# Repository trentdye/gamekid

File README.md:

# gamekid
Source files for my portable gaming device.

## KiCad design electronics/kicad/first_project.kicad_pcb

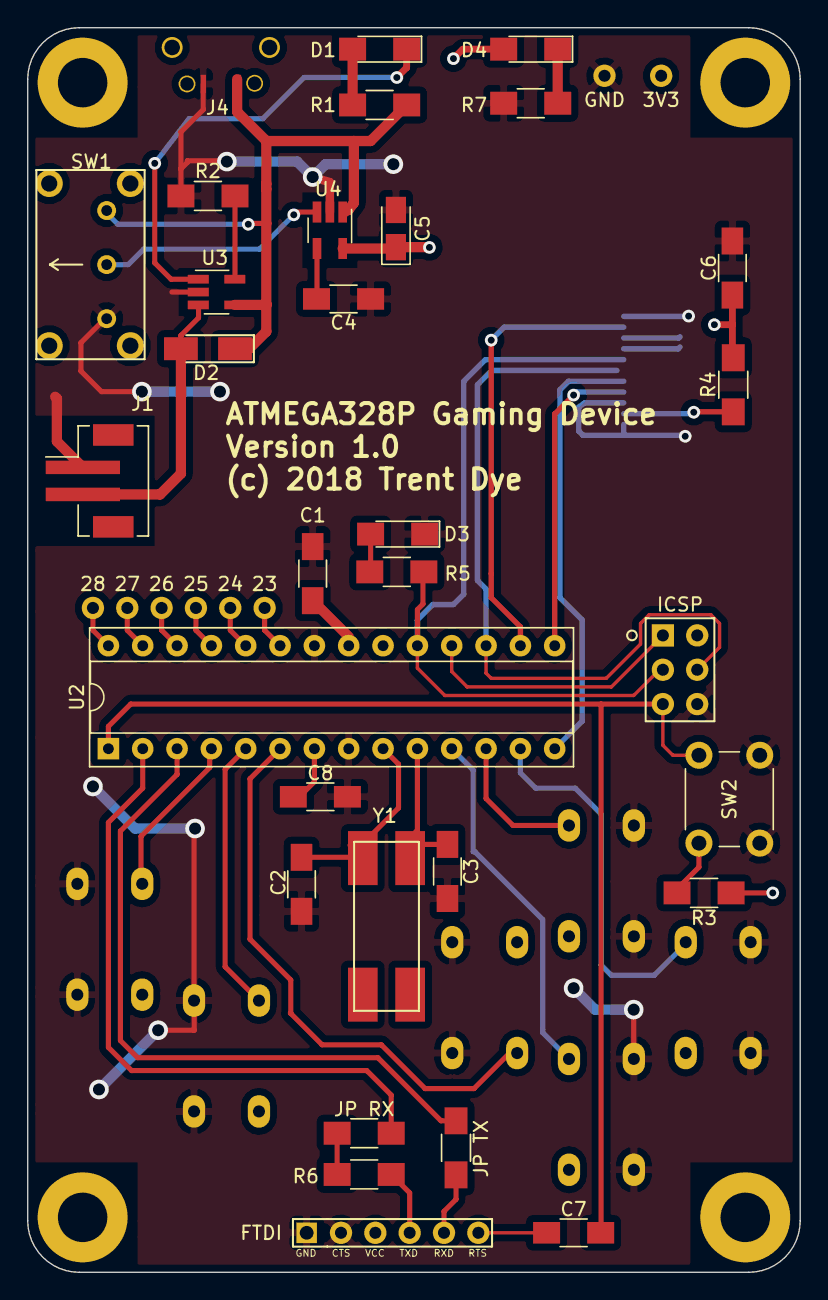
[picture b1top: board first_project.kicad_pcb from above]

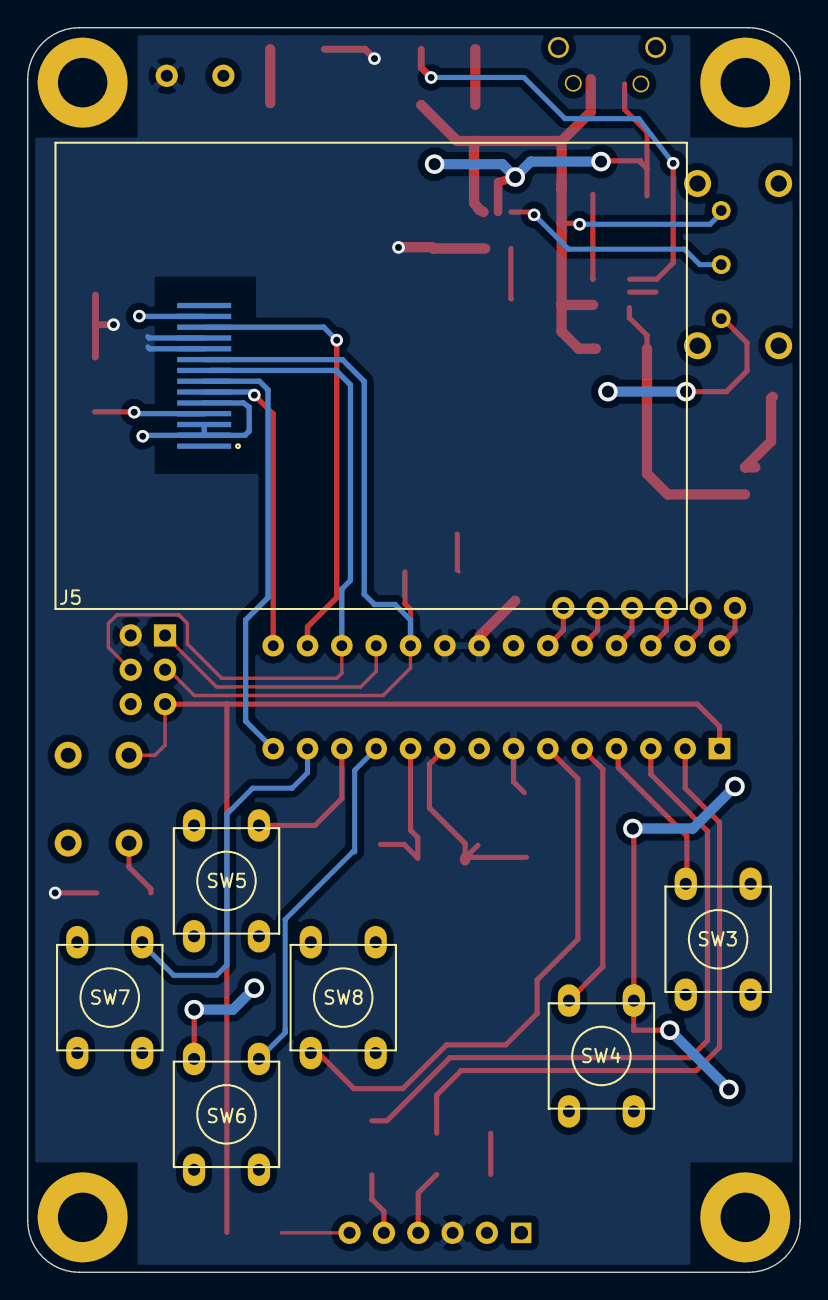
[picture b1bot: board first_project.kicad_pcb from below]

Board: 2 copper layers, 57.1 x 92.1 mm, 46 parts (7 on the bottom side), 39 nets.

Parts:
3V3: +3.3V; TP
23: PC0; TP
24: PC1; TP
25: PC2; TP
26: PC3; TP
27: PC4; TP
28: PC5; TP
C1, C7, C8: 0.1 uF; C_1206_HandSoldering
C2, C3: 20pF; C_1206_HandSoldering
C4: 470pf; C_1206_HandSoldering
C5: 10uF; CP_Tantalum_Case-S_EIA-3216-12_Reflow
C6: .1uF; C_1206_HandSoldering
D1, D3, D4: LED; LED_1206_HandSoldering
D2: B340A
FTDI: FTDI_HEADER
GND: TEST; TP
ICSP: ICSP_HEADER
J1: JST; JST_PH_B2B-PH-SM4-TB_02x2.00mm_Straight
J4: MICROUSB; 10118194-0001LF
J5: 1.8IN_TFT_ST7735_RIBBON; JDT-1800
JP RX: MCU_RXD; R_1206_HandSoldering
JP TX: MCU_TXD; R_1206_HandSoldering
R1: 330; R_1206_HandSoldering
R2: 10k; R_1206_HandSoldering
R3, R6: 10K; R_1206_HandSoldering
R4: 22; R_1206_HandSoldering
R5, R7: 60; R_1206_HandSoldering
SW1: 1825232-1; EG1224
SW2: 450-1647-ND; SW_PUSH_6mm_h4.3mm
SW3: BTN_A; ADAFRUIT_SOFT_TOUCH_BUTTON
SW4: BTN_B; ADAFRUIT_SOFT_TOUCH_BUTTON
SW5: BTN_U; ADAFRUIT_SOFT_TOUCH_BUTTON
SW6: BTN_D; ADAFRUIT_SOFT_TOUCH_BUTTON
SW7: BTN_L; ADAFRUIT_SOFT_TOUCH_BUTTON
SW8: BTN_R; ADAFRUIT_SOFT_TOUCH_BUTTON
U2: ATMEGA328P-PU; DIP-28_W7.62mm_Socket
U3: MCP73831; SOT-23-5_HandSoldering
U4: MIC5219-3.3; SOT-23-5_HandSoldering
Y1: CrystalSMD4Pin; ECS-80-16-28AX-TR

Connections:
+3V3: 3V3.1, C1.1, C5.1, C6.1, C8.1, D4.2, FTDI.3, ICSP.2, J5.10, J5.11, R3.1, R4.2, U2.7, U2.20, U2.21, U4.5
+BATT: D2.2, J1.2, U3.3
BUTTON_A: SW3.1, U2.4
BUTTON_B: SW4.1, U2.5
BUTTON_DOWN: SW6.1, U2.11
BUTTON_LEFT: SW7.1, U2.13
BUTTON_RIGHT: SW8.1, U2.6
BUTTON_UP: SW5.1, U2.12
CS: J5.12, U2.16
DISP_LED+: J5.4, R4.1
DISP_RESET: J5.6, U2.15
DISP_RS: J5.7, U2.14
GND: C1.2, C2.2, C3.2, C4.1, C5.2, C6.2, C8.2, D3.1, FTDI.1, FTDI.2, GND.1, ICSP.6, J1.1, J4.5, J5.2, J5.3, J5.5, J5.13, R2.1, R7.2, SW1.3, SW2.2, SW3.2, SW4.2, SW5.2, SW6.2, SW7.2, SW8.2, U2.8, U2.22, U3.2, U4.2
MCU_RESET: C7.2, ICSP.5, R3.2, SW2.1, U2.1
MISO: ICSP.1, U2.18
MOSI: ICSP.4, J5.8, U2.17
unnamed: C4.2, U4.4
unnamed: C7.1, FTDI.6
unnamed: D1.1, U3.1
unnamed: D1.2, R1.1
unnamed: D3.2, R5.1
unnamed: D4.1, R7.1
unnamed: FTDI.4, R6.1
unnamed: FTDI.5, JP TX.2
unnamed: JP RX.2, R6.2
unnamed: R2.2, U3.5
unnamed: SW1.2, U4.3
unnamed: 23.1, U2.23
unnamed: 24.1, U2.24
unnamed: 25.1, U2.25
unnamed: 26.1, U2.26
unnamed: 27.1, U2.27
unnamed: 28.1, U2.28
RXD: JP RX.1, U2.2
SCK: ICSP.3, J5.9, R5.2, U2.19
TXD: JP TX.1, U2.3
VBUS: D2.1, J4.1, R1.2, SW1.1, U3.4, U4.1
XTAL1: C2.1, U2.9, Y1.1
XTAL2: C3.1, U2.10, Y1.4

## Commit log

2018-05-16 Added source code and (e)CAD files.
2018-05-16 Added BOM
2018-08-16 Add project documentation document
2018-08-16 Add project documentation file to top level

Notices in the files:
electronics/kicad/first_project.kicad_pcb:
(c) 2018 Trent Dye
